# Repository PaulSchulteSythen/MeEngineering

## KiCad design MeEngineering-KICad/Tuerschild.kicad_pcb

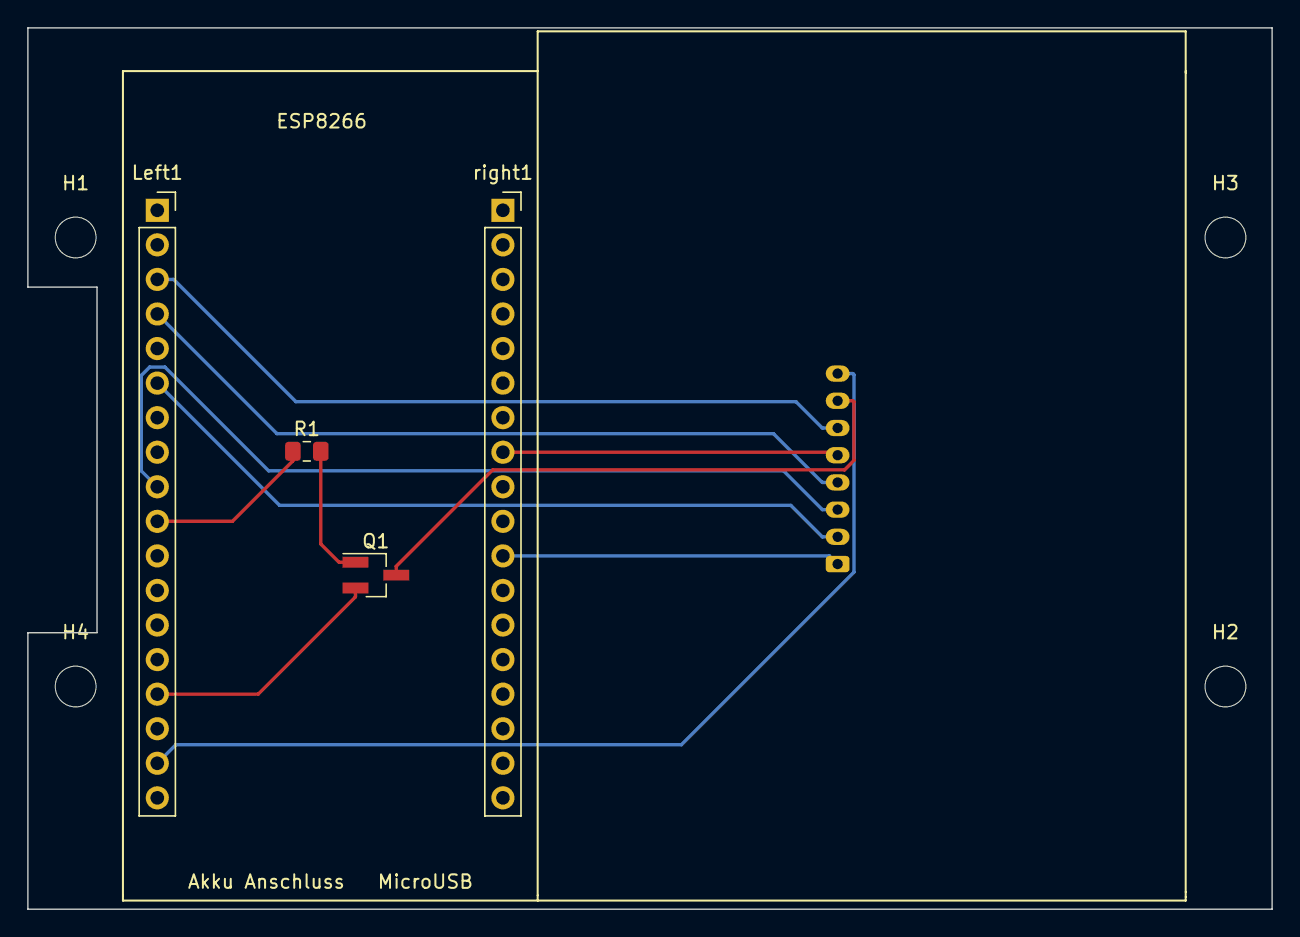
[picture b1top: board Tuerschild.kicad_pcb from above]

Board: 2 copper layers, 91.4 x 64.8 mm, 9 parts (1 on the bottom side), 11 nets.

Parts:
H1, H2, H3, H4: MountingHole; MountingHole_3mm
J3: Conn_01x08; JST_PH_S8B-PH-K_1x08_P2.00mm_Horizontal
Left1: Conn_01x18_Female; PinSocket_1x18_P2.54mm_Vertical
Q1: 2N7002K; SOT-23_Handsoldering
R1: R; R_0805_2012Metric_Pad1.15x1.40mm_HandSolder
right1: Conn_01x18_Female; PinSocket_1x18_P2.54mm_Vertical

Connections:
unnamed: J3.1, right1.11
unnamed: J3.2, Left1.6
unnamed: J3.3, Left1.9
unnamed: J3.4, Left1.4
unnamed: J3.5, right1.8
unnamed: J3.6, Left1.3
unnamed: J3.7, Q1.3
unnamed: J3.8, Left1.17
unnamed: Left1.10, R1.1
unnamed: Left1.15, Q1.2
unnamed: Q1.1, R1.2
